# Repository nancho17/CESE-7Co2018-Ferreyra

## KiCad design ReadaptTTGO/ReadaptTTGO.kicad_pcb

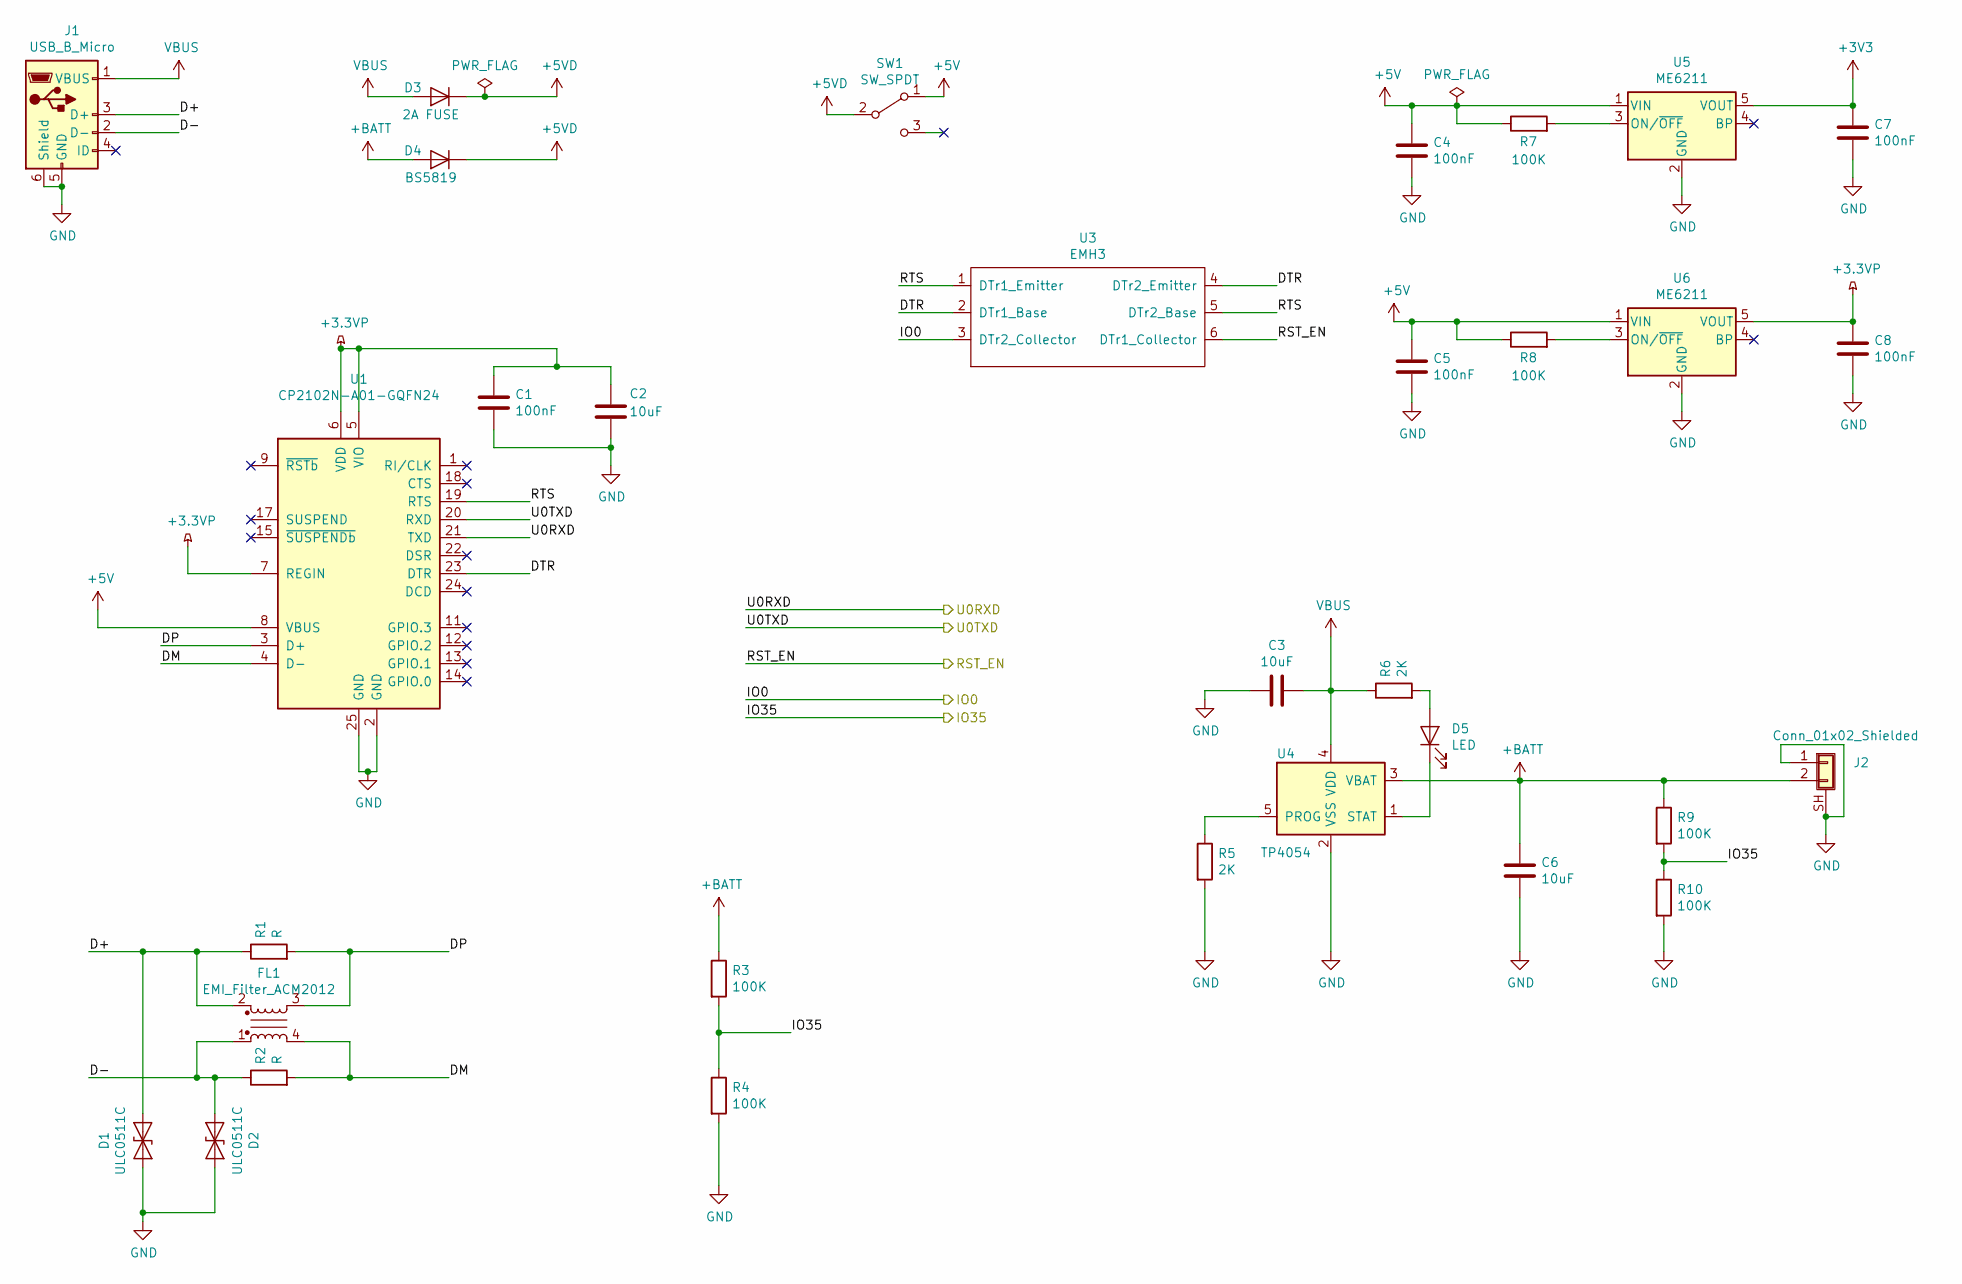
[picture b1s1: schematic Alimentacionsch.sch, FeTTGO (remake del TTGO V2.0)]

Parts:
C1: 100nF; C_0201_0603Metric
C2: 10uF; C_01005_0402Metric
C3, C6: 10uF; C_0201_0603Metric
C4, C5, C7, C8: 100nF; C_01005_0402Metric
D1, D2: ULC0511C; D_01005_0402Metric
D3: 2A FUSE; D_SOD-123
D4: BS5819; D_SOD-123
D5: LED; LED_0201_0603Metric
FL1: EMI_Filter_ACM2012; Filter_Bourns_SRF0905_6.0x9.2mm
J1: USB_B_Micro; USB_Micro-B_Amphenol_10103594-0001LF_Horizontal
J2: Conn_01x02_Shielded; BarrelJack_Wuerth_6941xx301002
R1, R2: R; R_01005_0402Metric
R3, R4, R7, R8, R9, R10: 100K; R_01005_0402Metric
R5, R6: 2K; R_01005_0402Metric
SW1: SW_SPDT; SW_CuK_OS102011MA1QN1_SPDT_Angled
U1: CP2102N-A01-GQFN24; QFN-24-1EP_4x4mm_P0.5mm_EP2.6x2.6mm
U3: EMH3; SOT-563
U4: TP4054; SOT-23-5
U5, U6: ME6211; SOT-23-5

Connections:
+3.3VP: C1.1, C2.1, C8.1, U1.5 (VIO), U1.6 (VDD), U1.7 (REGIN), U6.5 (VOUT); also elsewhere on the board
+3V3: C7.1, U5.5 (VOUT); also elsewhere on the board
+5V: C4.1, C5.1, R7.1, R8.1, SW1.1 (A), U1.8 (VBUS), U5.1 (VIN), U6.1 (VIN); also elsewhere on the board
+5VD: D3.1 (K), D4.1 (K), SW1.2 (B)
+BATT: C6.1, D4.2 (A), J2.2, R3.1, R9.1, U4.3 (VBAT)
/Power/D+: D1.2 (A2), FL1.2, J1.3 (D+), R1.1
/Power/D-: D2.1 (A1), FL1.1, J1.2 (D-), R2.1
/Power/DM: FL1.4, R2.2, U1.4 (D-)
/Power/DP: FL1.3, R1.2, U1.3 (D+)
/Power/DTR: U1.23 (DTR), U3.2 (DTr1_Base), U3.4 (DTr2_Emitter)
/Power/IO0: U3.3 (DTr2_Collector); also elsewhere on the board
/Power/IO35: R3.2, R4.1, R9.2, R10.1; also elsewhere on the board
/Power/RST_EN: U3.6 (DTr1_Collector); also elsewhere on the board
/Power/RTS: U1.19 (RTS), U3.1 (DTr1_Emitter), U3.5 (DTr2_Base)
/Power/U0RXD: U1.21 (TXD); also elsewhere on the board
/micro/U0RXD: U1.20 (RXD); also elsewhere on the board
GND: C1.2, C2.2, C3.2, C4.2, C5.2, C6.2, C7.2, C8.2, D1.1 (A1), D2.2 (A2), J1.5 (GND), J1.6 (Shield), J2.1, J2.SH (Shield), R4.2, R5.2, R10.2, U1.2 (GND), U1.25 (GND), U4.2 (VSS), U5.2 (GND), U6.2 (GND); also elsewhere on the board
unnamed: D5.1 (K), U4.1 (STAT)
unnamed: D5.2 (A), R6.2
unnamed: R5.1, U4.5 (PROG)
unnamed: R7.2, U5.3 (ON/~OFF~)
unnamed: R8.2, U6.3 (ON/~OFF~)
VBUS: C3.1, D3.2 (A), J1.1 (VBUS), R6.1, U4.4 (VDD)

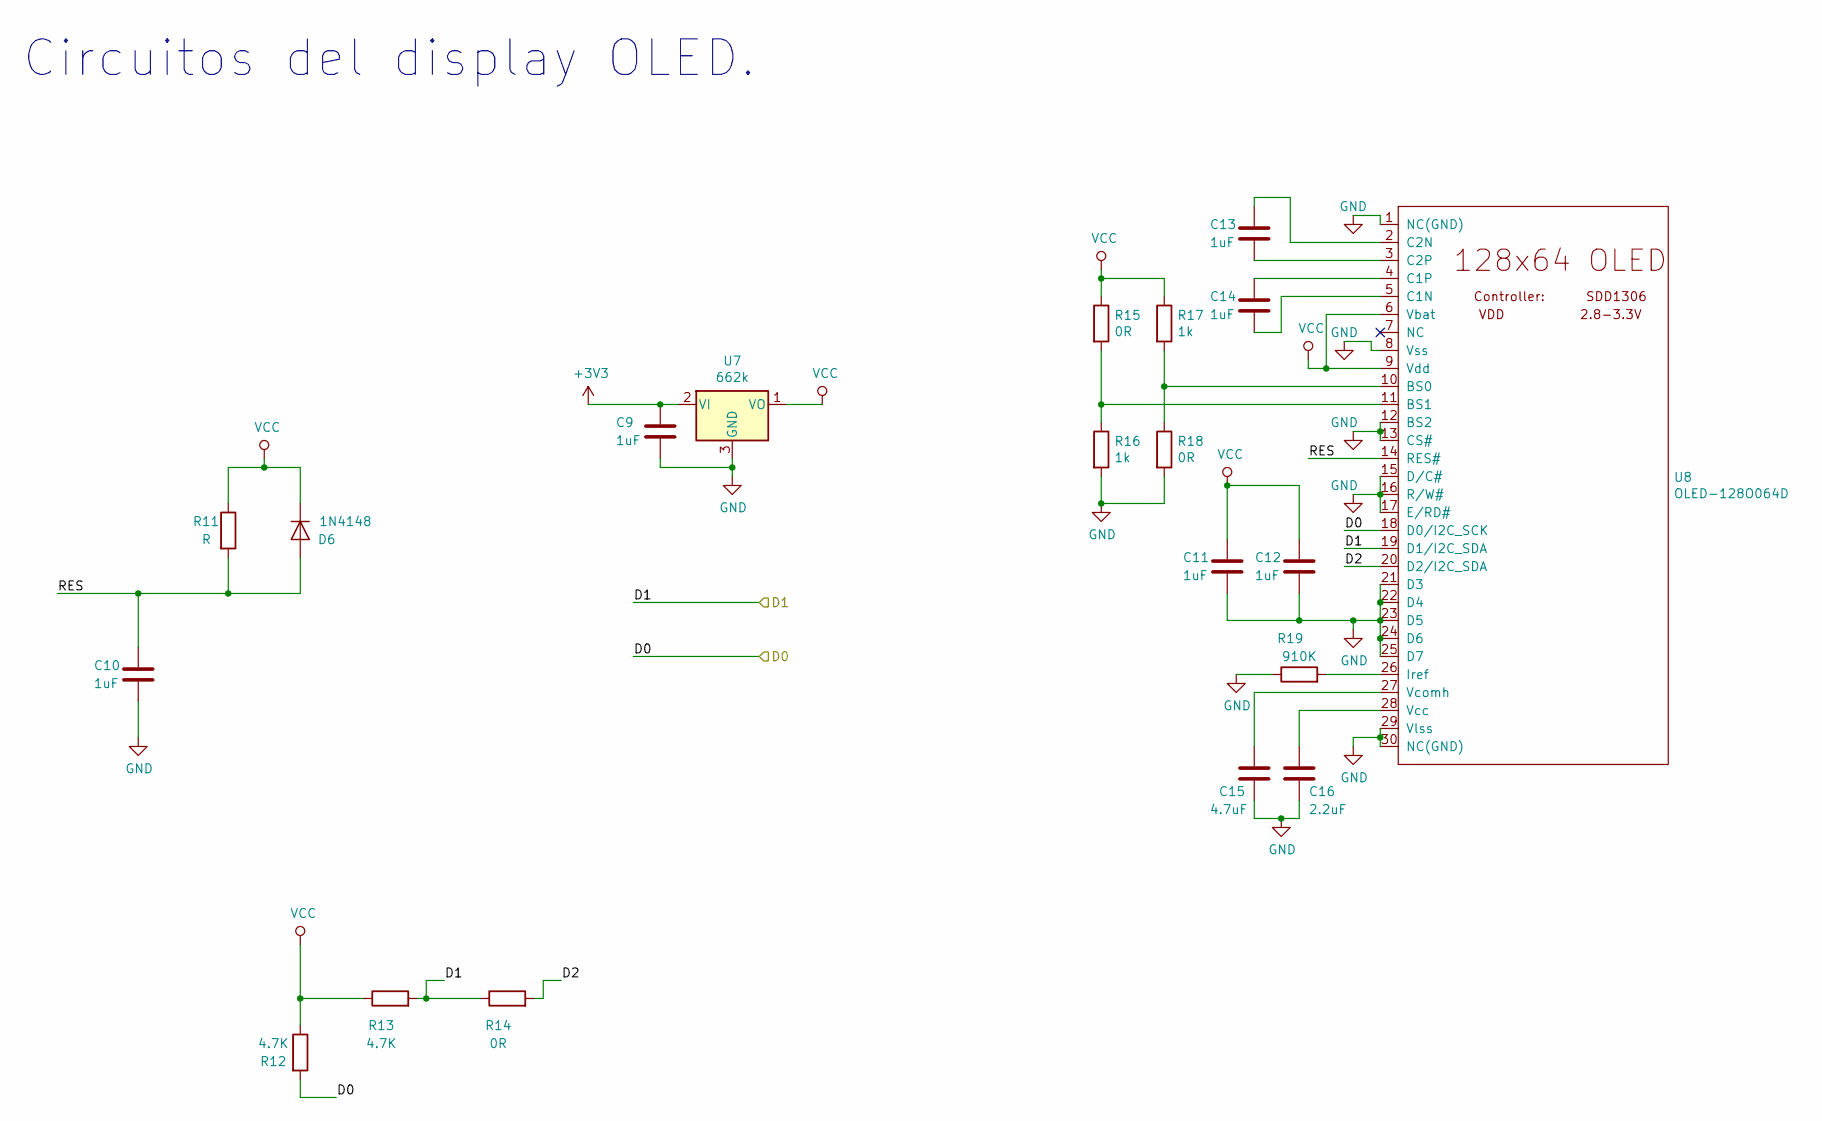
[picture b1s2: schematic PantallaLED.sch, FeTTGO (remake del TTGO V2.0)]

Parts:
C9, C10, C11, C12, C13, C14: 1uF; C_01005_0402Metric
C15: 4.7uF; C_0201_0603Metric
C16: 2.2uF; C_0201_0603Metric
D6: 1N4148; D_SOD-323
R11: R; R_01005_0402Metric
R12, R13: 4.7K; R_01005_0402Metric
R14, R15, R18: 0R; R_01005_0402Metric
R16, R17: 1k; R_01005_0402Metric
R19: 910K; R_01005_0402Metric
U7: 662k; SOT-23
U8: OLED-128O064D; Molex_200528-0300_1x30-1MP_P1.00mm_Horizontal

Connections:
+3V3: C9.1, U7.2 (VI); also elsewhere on the board
/LEDscreen/D0: R12.2, U8.18 (D0/I2C_SCK); also elsewhere on the board
/LEDscreen/D1: R13.2, R14.1, U8.19 (D1/I2C_SDA); also elsewhere on the board
/LEDscreen/D2: R14.2, U8.20 (D2/I2C_SDA)
GND: C9.2, C10.2, C11.2, C12.2, C15.2, C16.2, R16.2, R18.2, R19.1, U7.3 (GND), U8.1 (NC(GND)), U8.8 (Vss), U8.12 (BS2), U8.13 (CS#), U8.15 (D/C#), U8.16 (R/W#), U8.17 (E/RD#), U8.21 (D3), U8.22 (D4), U8.23 (D5), U8.24 (D6), U8.25 (D7), U8.29 (Vlss), U8.30 (NC(GND)); also elsewhere on the board
unnamed: C13.1, U8.2 (C2N)
unnamed: C13.2, U8.3 (C2P)
unnamed: C14.1, U8.4 (C1P)
unnamed: C14.2, U8.5 (C1N)
unnamed: C15.1, U8.27 (Vcomh)
unnamed: C16.1, U8.28 (Vcc)
unnamed: R15.2, R16.1, U8.11 (BS1)
unnamed: R17.2, R18.1, U8.10 (BS0)
unnamed: R19.2, U8.26 (Iref)

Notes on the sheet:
Circuitos del display OLED.

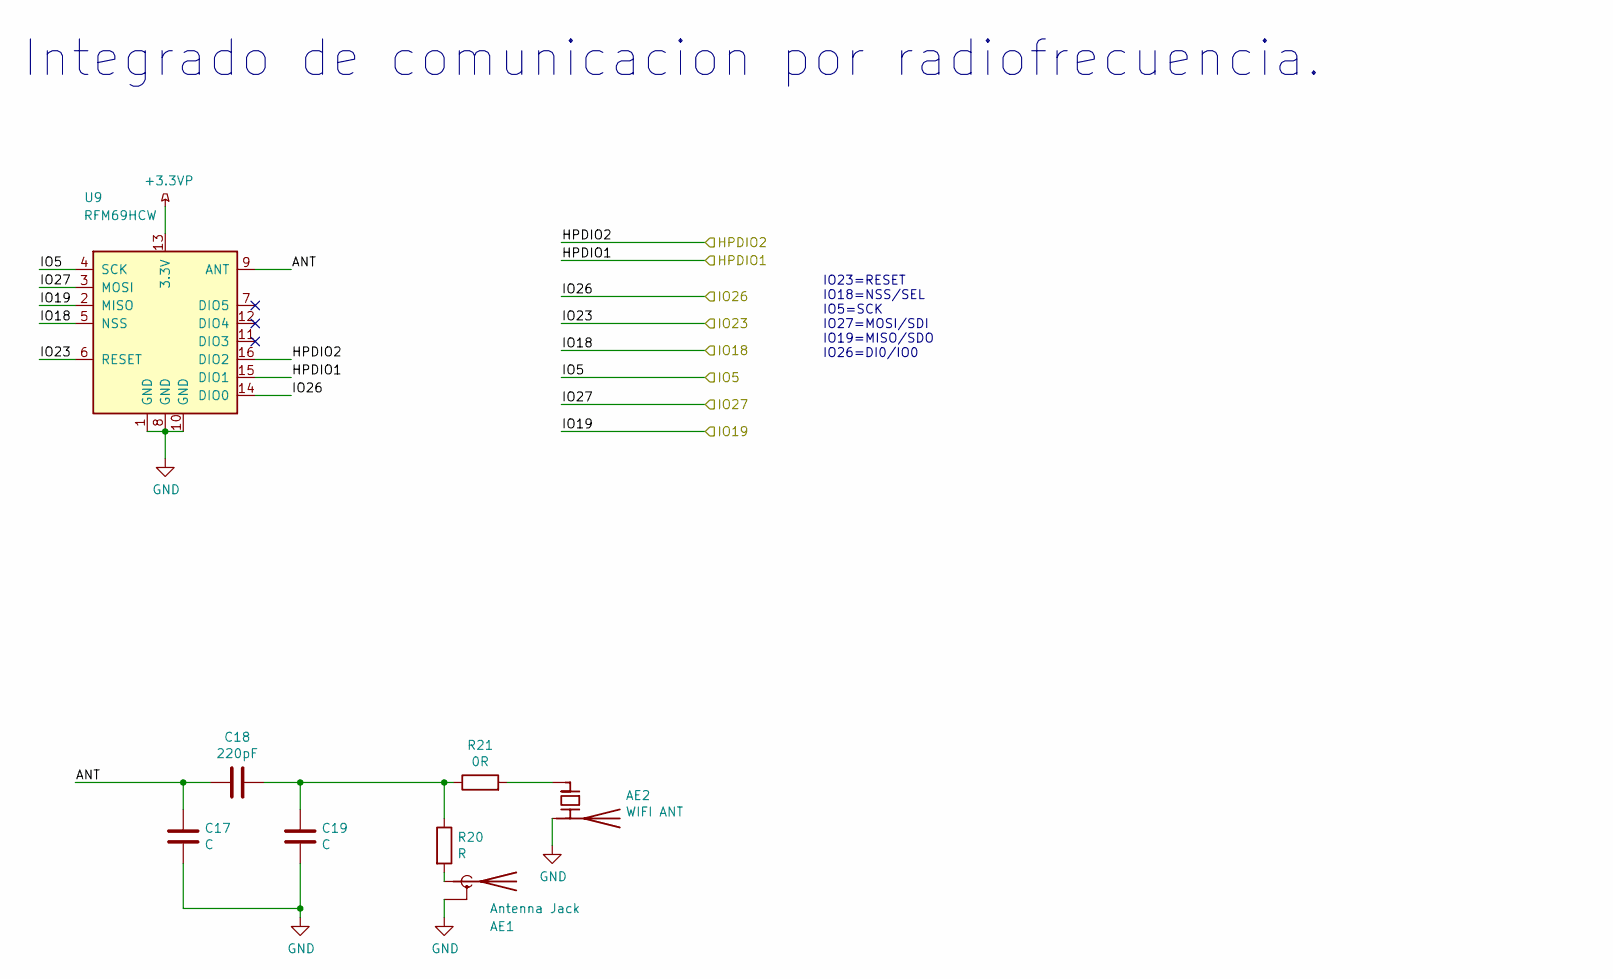
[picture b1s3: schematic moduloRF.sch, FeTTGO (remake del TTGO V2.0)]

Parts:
AE1: Antenna Jack; SMA_Amphenol_132134_Vertical
AE2: WIFI ANT; SMA_Amphenol_132134_Vertical
C17, C19: C; C_01005_0402Metric
C18: 220pF; C_01005_0402Metric
R20: R; R_01005_0402Metric
R21: 0R; R_01005_0402Metric
U9: RFM69HCW; HOPERF_RFM69HW

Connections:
+3.3VP: U9.13 (3.3V); also elsewhere on the board
/micro/HPDIO1: U9.15 (DIO1); also elsewhere on the board
/micro/HPDIO2: U9.16 (DIO2); also elsewhere on the board
/micro/IO5: U9.4 (SCK); also elsewhere on the board
/micro/IO18: U9.5 (NSS); also elsewhere on the board
/micro/IO19: U9.2 (MISO); also elsewhere on the board
/micro/IO23: U9.6 (RESET); also elsewhere on the board
/micro/IO26: U9.14 (DIO0); also elsewhere on the board
/micro/IO27: U9.3 (MOSI); also elsewhere on the board
/moduloRF/ANT: C17.1, C18.2, U9.9 (ANT)
GND: AE1.2 (Shield), AE2.2 (PCB_Trace), C17.2, C19.2, U9.1 (GND), U9.8 (GND), U9.10 (GND); also elsewhere on the board
unnamed: AE1.1 (A), R20.2
unnamed: AE2.1 (FEED), R21.2
unnamed: C18.1, C19.1, R20.1, R21.1

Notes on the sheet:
IO23=RESET IO18=NSS/SEL IO5=SCK IO27=MOSI/SDI IO19=MISO/SDO IO26=DI0/IO0
Integrado de comunicacion por radiofrecuencia.

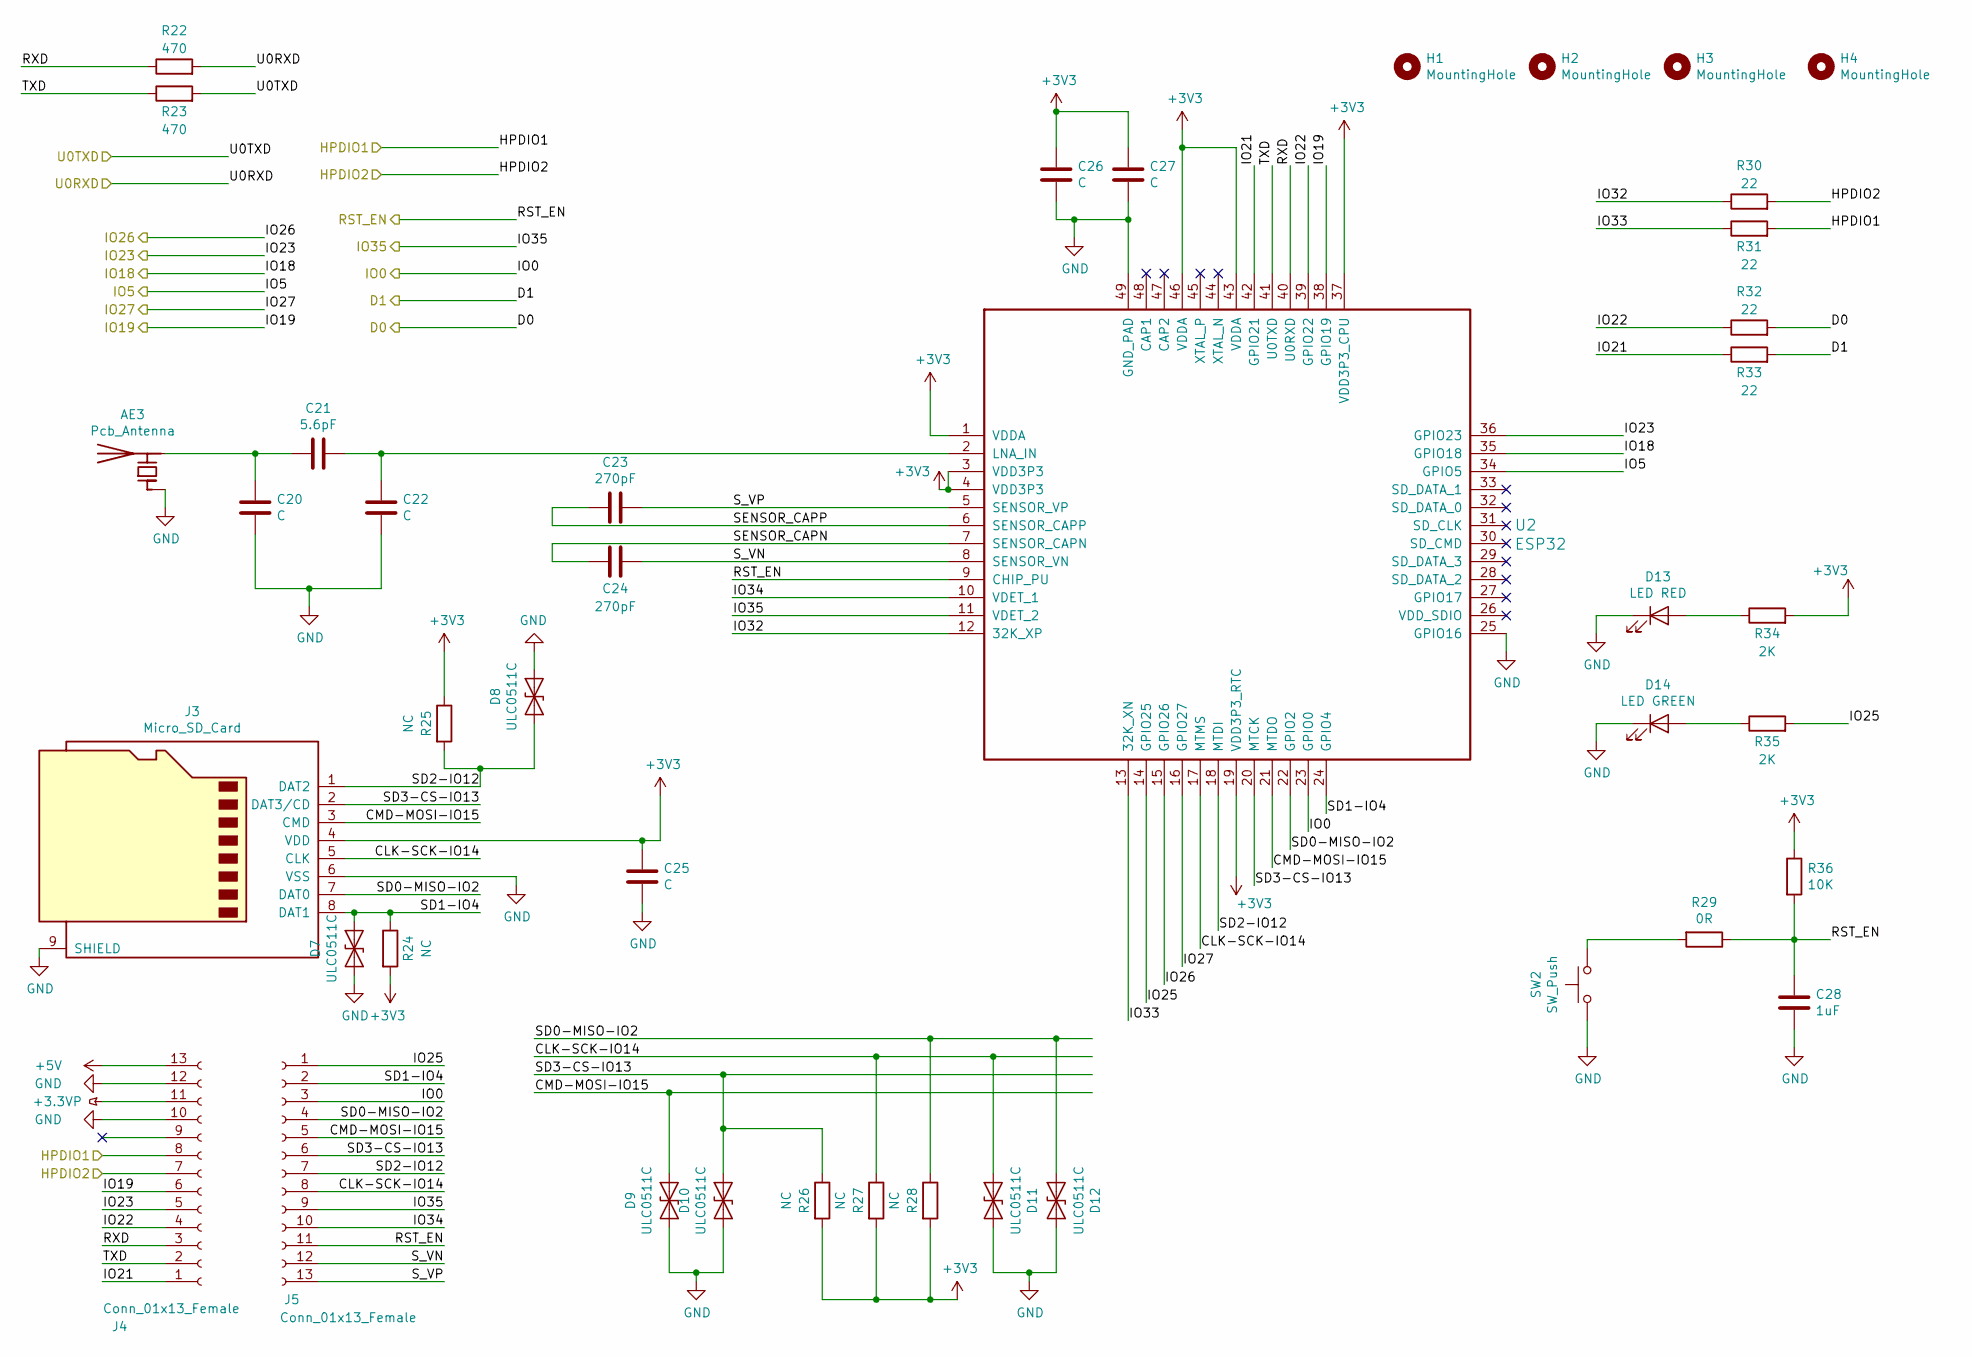
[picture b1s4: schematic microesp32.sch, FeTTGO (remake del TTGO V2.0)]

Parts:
AE3: Pcb_Antenna; SWRA117D
C20, C22, C25, C27: C; C_01005_0402Metric
C21: 5.6pF; C_01005_0402Metric
C23, C24: 270pF; C_01005_0402Metric
C26: C; C_0201_0603Metric
C28: 1uF; C_01005_0402Metric
D7, D8, D9, D10, D11, D12: ULC0511C; D_01005_0402Metric
D13: LED RED; LED_0201_0603Metric
D14: LED GREEN; LED_0201_0603Metric
H1, H2, H3, H4: MountingHole; Fiducial_1mm_Mask2mm
J3: Micro_SD_Card; microSD_HC_Hirose_DM3D-SF
J4, J5: Conn_01x13_Female; TerminalBlock_Phoenix_PT-1,5-13-5.0-H_1x13_P5.00mm_Horizont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
R22, R23: 470; R_01005_0402Metric
R24, R25, R26, R27, R28: NC; R_01005_0402Metric
R29: 0R; R_01005_0402Metric
R30, R31, R32, R33: 22; R_01005_0402Metric
R34, R35: 2K; R_01005_0402Metric
R36: 10K; R_01005_0402Metric
SW2: SW_Push; SW_Push_1P1T_NO_6x6mm_H9.5mm
U2: ESP32; UQFN-48-1EP_6x6mm_P0.4mm_EP4.45x4.45mm

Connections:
+3.3VP: J4.11; also elsewhere on the board
+3V3: C25.1, C26.1, C27.1, J3.4 (VDD), R24.2, R25.1, R26.2, R27.2, R28.2, R34.2, R36.1, U2.1 (VDDA), U2.3 (VDD3P3), U2.4 (VDD3P3), U2.19 (VDD3P3_RTC), U2.37 (VDD3P3_CPU), U2.43 (VDDA), U2.46 (VDDA); also elsewhere on the board
+5V: J4.13; also elsewhere on the board
/LEDscreen/D0: R32.2; also elsewhere on the board
/LEDscreen/D1: R33.2; also elsewhere on the board
/Power/IO0: J5.3, U2.23 (GPIO0); also elsewhere on the board
/Power/IO35: J5.9, U2.11 (VDET_2); also elsewhere on the board
/Power/RST_EN: C28.1, J5.11, R29.1, R36.2, U2.9 (CHIP_PU); also elsewhere on the board
/Power/U0RXD: R23.2; also elsewhere on the board
/micro/CLK-SCK-IO14: D11.1 (A1), J3.5 (CLK), J5.8, R27.1, U2.17 (MTMS)
/micro/CMD-MOSI-IO15: D9.2 (A2), J3.3 (CMD), J5.5, U2.21 (MTDO)
/micro/HPDIO1: J4.8, R31.2; also elsewhere on the board
/micro/HPDIO2: J4.7, R30.2; also elsewhere on the board
/micro/IO5: U2.34 (GPIO5); also elsewhere on the board
/micro/IO18: U2.35 (GPIO18); also elsewhere on the board
/micro/IO19: J4.6, U2.38 (GPIO19); also elsewhere on the board
/micro/IO21: J4.1, R33.1, U2.42 (GPIO21)
/micro/IO22: J4.4, R32.1, U2.39 (GPIO22)
/micro/IO23: J4.5, U2.36 (GPIO23); also elsewhere on the board
/micro/IO25: J5.1, R35.2, U2.14 (GPIO25)
/micro/IO26: U2.15 (GPIO26); also elsewhere on the board
/micro/IO27: U2.16 (GPIO27); also elsewhere on the board
/micro/IO32: R30.1, U2.12 (32K_XP)
/micro/IO33: R31.1, U2.13 (32K_XN)
/micro/IO34: J5.10, U2.10 (VDET_1)
/micro/RXD: J4.3, R22.1, U2.40 (U0RXD)
/micro/SD0-MISO-IO2: D12.1 (A1), J3.7 (DAT0), J5.4, R28.1, U2.22 (GPIO2)
/micro/SD1-IO4: D7.2 (A2), J3.8 (DAT1), J5.2, R24.1, U2.24 (GPIO4)
/micro/SD2-IO12: D8.1 (A1), J3.1 (DAT2), J5.7, R25.2, U2.18 (MTDI)
/micro/SD3-CS-IO13: D10.2 (A2), J3.2 (DAT3/CD), J5.6, R26.1, U2.20 (MTCK)
/micro/SENSOR_CAPN: C24.2, U2.7 (SENSOR_CAPN)
/micro/SENSOR_CAPP: C23.2, U2.6 (SENSOR_CAPP)
/micro/S_VN: C24.1, J5.12, U2.8 (SENSOR_VN)
/micro/S_VP: C23.1, J5.13, U2.5 (SENSOR_VP)
/micro/TXD: J4.2, R23.1, U2.41 (U0TXD)
/micro/U0RXD: R22.2; also elsewhere on the board
GND: AE3.1 (FEED), C20.2, C22.2, C25.2, C26.2, C27.2, C28.2, D7.1 (A1), D8.2 (A2), D9.1 (A1), D10.1 (A1), D11.2 (A2), D12.2 (A2), D13.1 (K), D14.1 (K), J3.6 (VSS), J3.9 (SHIELD), J4.10, J4.12, SW2.1, U2.25 (GPIO16), U2.49 (GND_PAD); also elsewhere on the board
unnamed: AE3.2 (PCB_Trace), C20.1, C21.2
unnamed: C21.1, C22.1, U2.2 (LNA_IN)
unnamed: D13.2 (A), R34.1
unnamed: D14.2 (A), R35.1
unnamed: R29.2, SW2.2

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
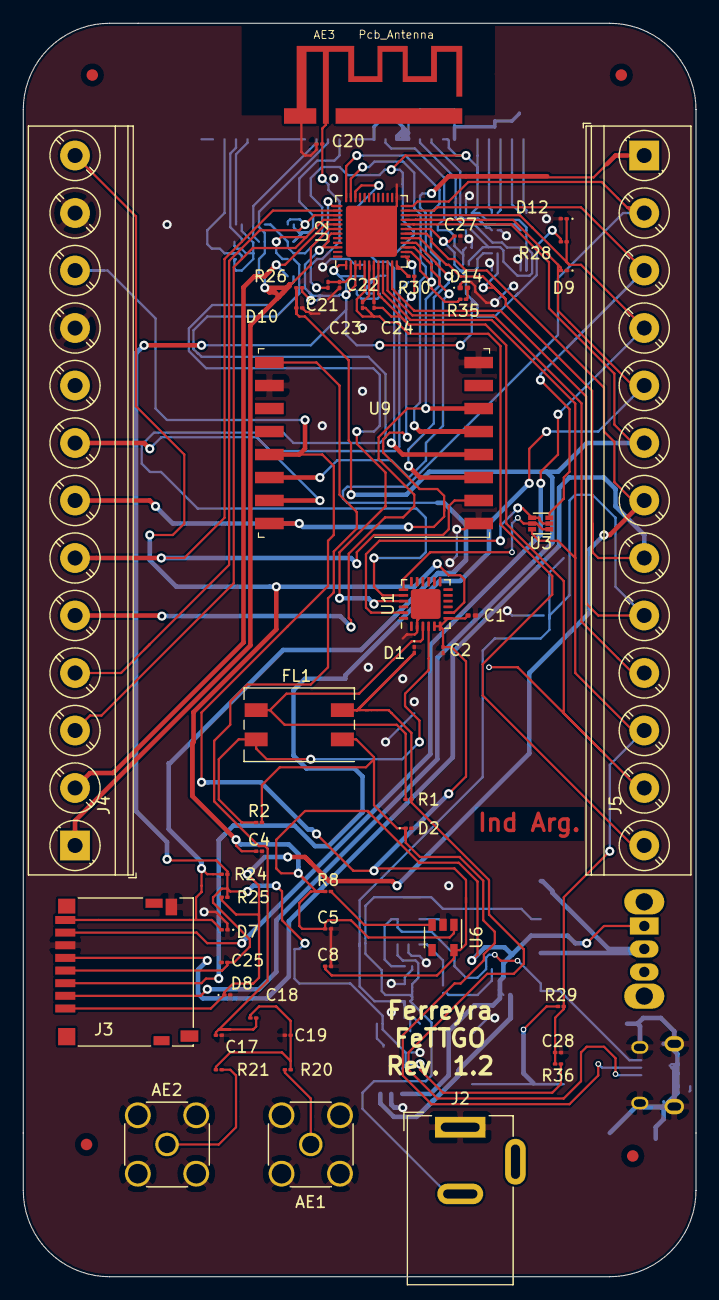
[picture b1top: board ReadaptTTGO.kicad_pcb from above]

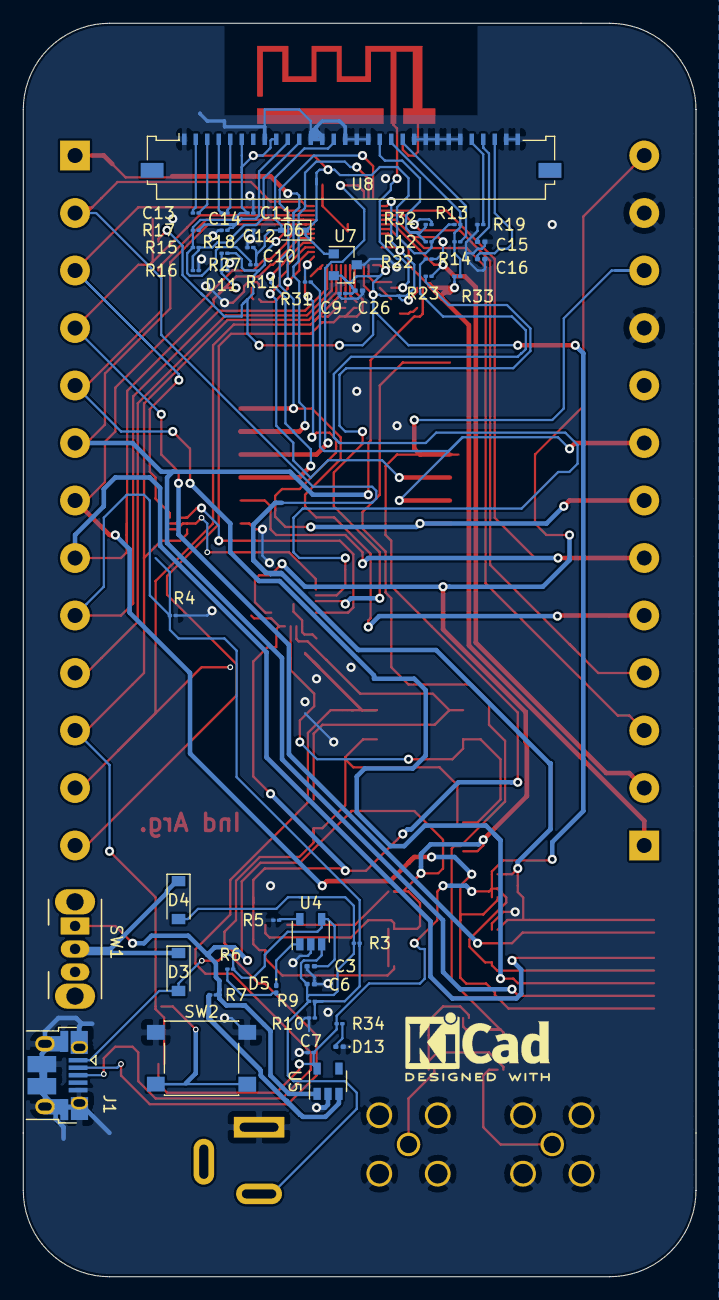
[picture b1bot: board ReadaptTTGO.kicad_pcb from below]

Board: 2 copper layers, 58.5 x 109.0 mm, 102 parts (48 on the bottom side), 72 nets.

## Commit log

2019-06-19 no an
2019-07-02 Primer aproximacion.
2019-07-02 Anotacciones
2019-07-02 ERC completo
2019-07-02 Añadidos Footprints
2019-07-06 Comienzo PCB
2019-07-08 PCB sin traces
2019-07-09 Pre aplicacion de las zonas de relleno
2019-07-09 PCB Para revision
2019-07-13 Agregado componentes 3d, serigrafia
2019-07-13 Entrega revision 1.2
